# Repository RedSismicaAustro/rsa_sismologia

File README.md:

# RSA Sismología (`rsa_sismologia`)

Sistema de análisis sismológico, procesamiento de señales sísmicas (MiniSEED/EVT), marcado de fases y generación de boletines oficiales de la Red Sísmica del Austro (RSA).

---

## 📚 Documentación y Manuales del Sistema

- **Manual y Reglas del Agente**: [`AGENTS.md`](file:///c:/proyectos/rsa_sismologia/AGENTS.md)
- **Contexto Técnico Maestro**: [`docs/contexto_maestro_agente.md`](file:///c:/proyectos/rsa_sismologia/docs/contexto_maestro_agente.md)
- **Estructura de Datos `DIA`**: [`docs/contexto_estructura_datos_dia.md`](file:///c:/proyectos/rsa_sismologia/docs/contexto_estructura_datos_dia.md)
- **Archivos de Configuración**: [`docs/contexto_archivos_configuracion_datos.md`](file:///c:/proyectos/rsa_sismologia/docs/contexto_archivos_configuracion_datos.md)

---

## 🔄 Protocolo de Sesión con Agentes IA

### 🟢 Inicio de Sesión (Scope Lock):
```text
Considera las reglas y skills definidos en .agents/rules y .agents/skills.
Para esta sesión, nuestro directorio de trabajo exclusivo será [DIRECTORIO]. No modifiques ni busques archivos fuera de esta ruta a menos que te lo pida. 
Revisa los archivos del directorio [DIRECTORIO] para que entiendas el contexto actual del proyecto. Todavia no modifiques ni crees ningun archivo.
```

### 🔴 Cierre de Sesión:
1. `Genera o actualiza el contexto tecnico de los archivos que fueron modificados durante la sesión, según la skill generar_contexto.md.`
2. `Extrae o actualiza el ADR de las decisiones tomadas durante la sesión, según la skill extraer_adr.md.`
3. `Genera la transición técnica de esta sesión según la skill crear_transicion_tecnica.md.`
4. `Genera un resumen detallado de todos los cambios y archivos modificados durante esta sesión.`

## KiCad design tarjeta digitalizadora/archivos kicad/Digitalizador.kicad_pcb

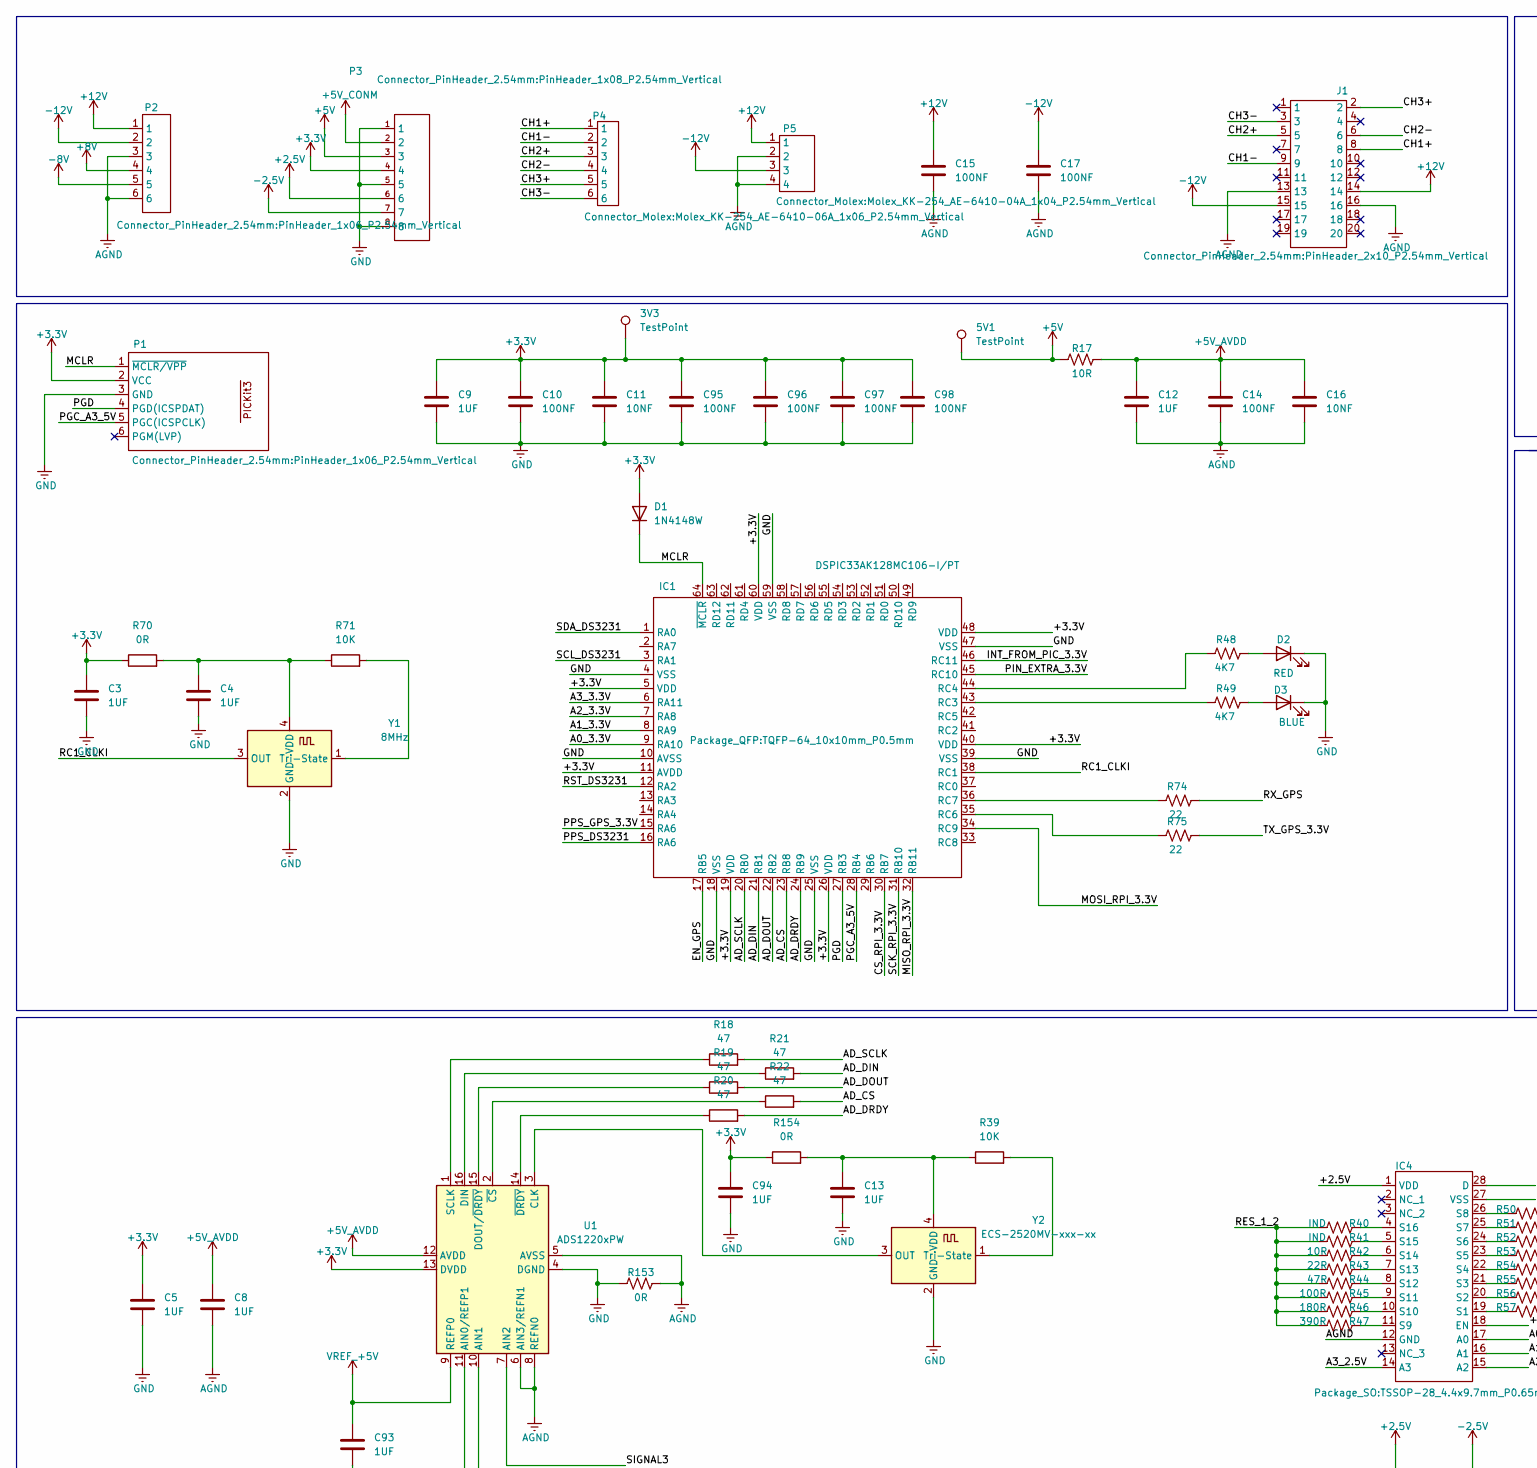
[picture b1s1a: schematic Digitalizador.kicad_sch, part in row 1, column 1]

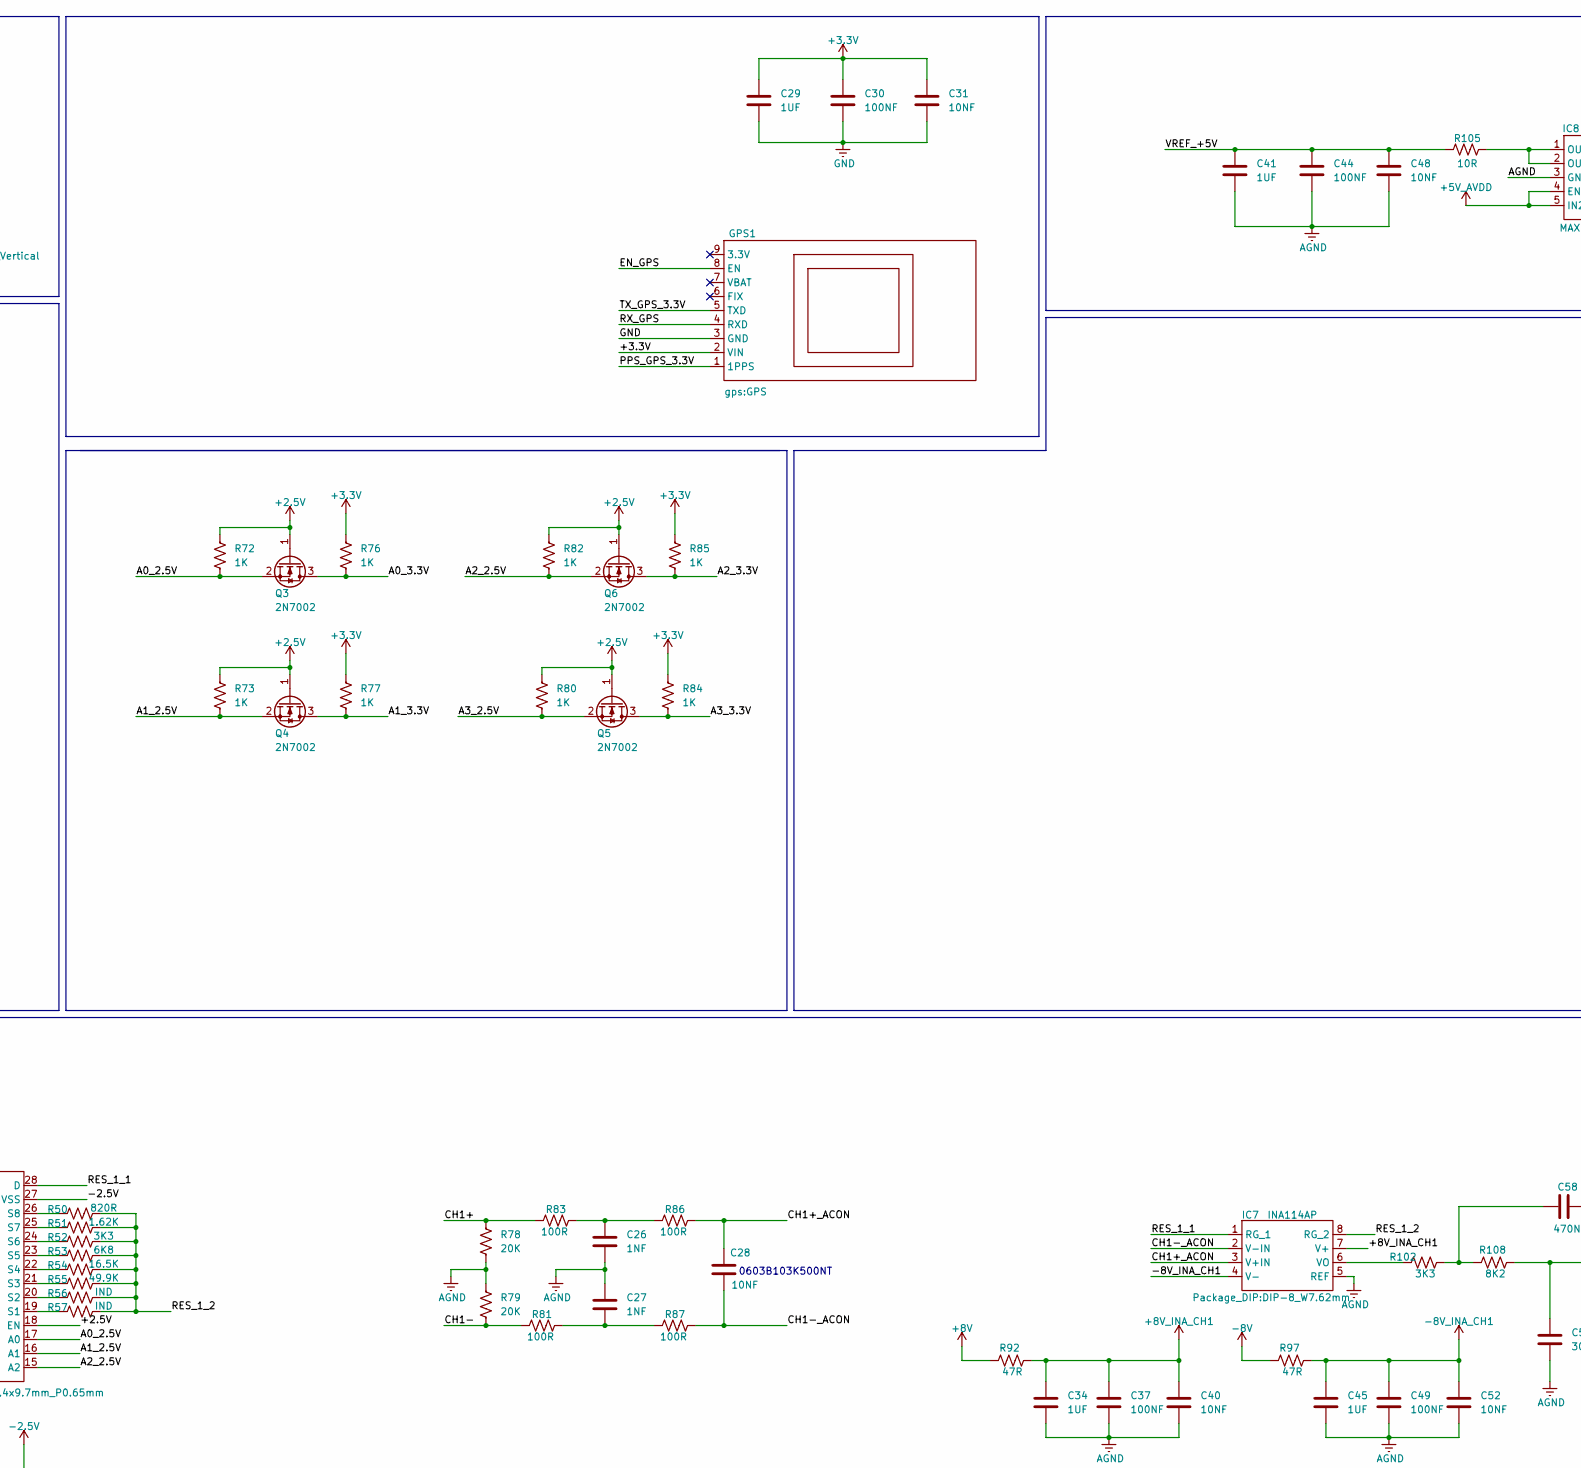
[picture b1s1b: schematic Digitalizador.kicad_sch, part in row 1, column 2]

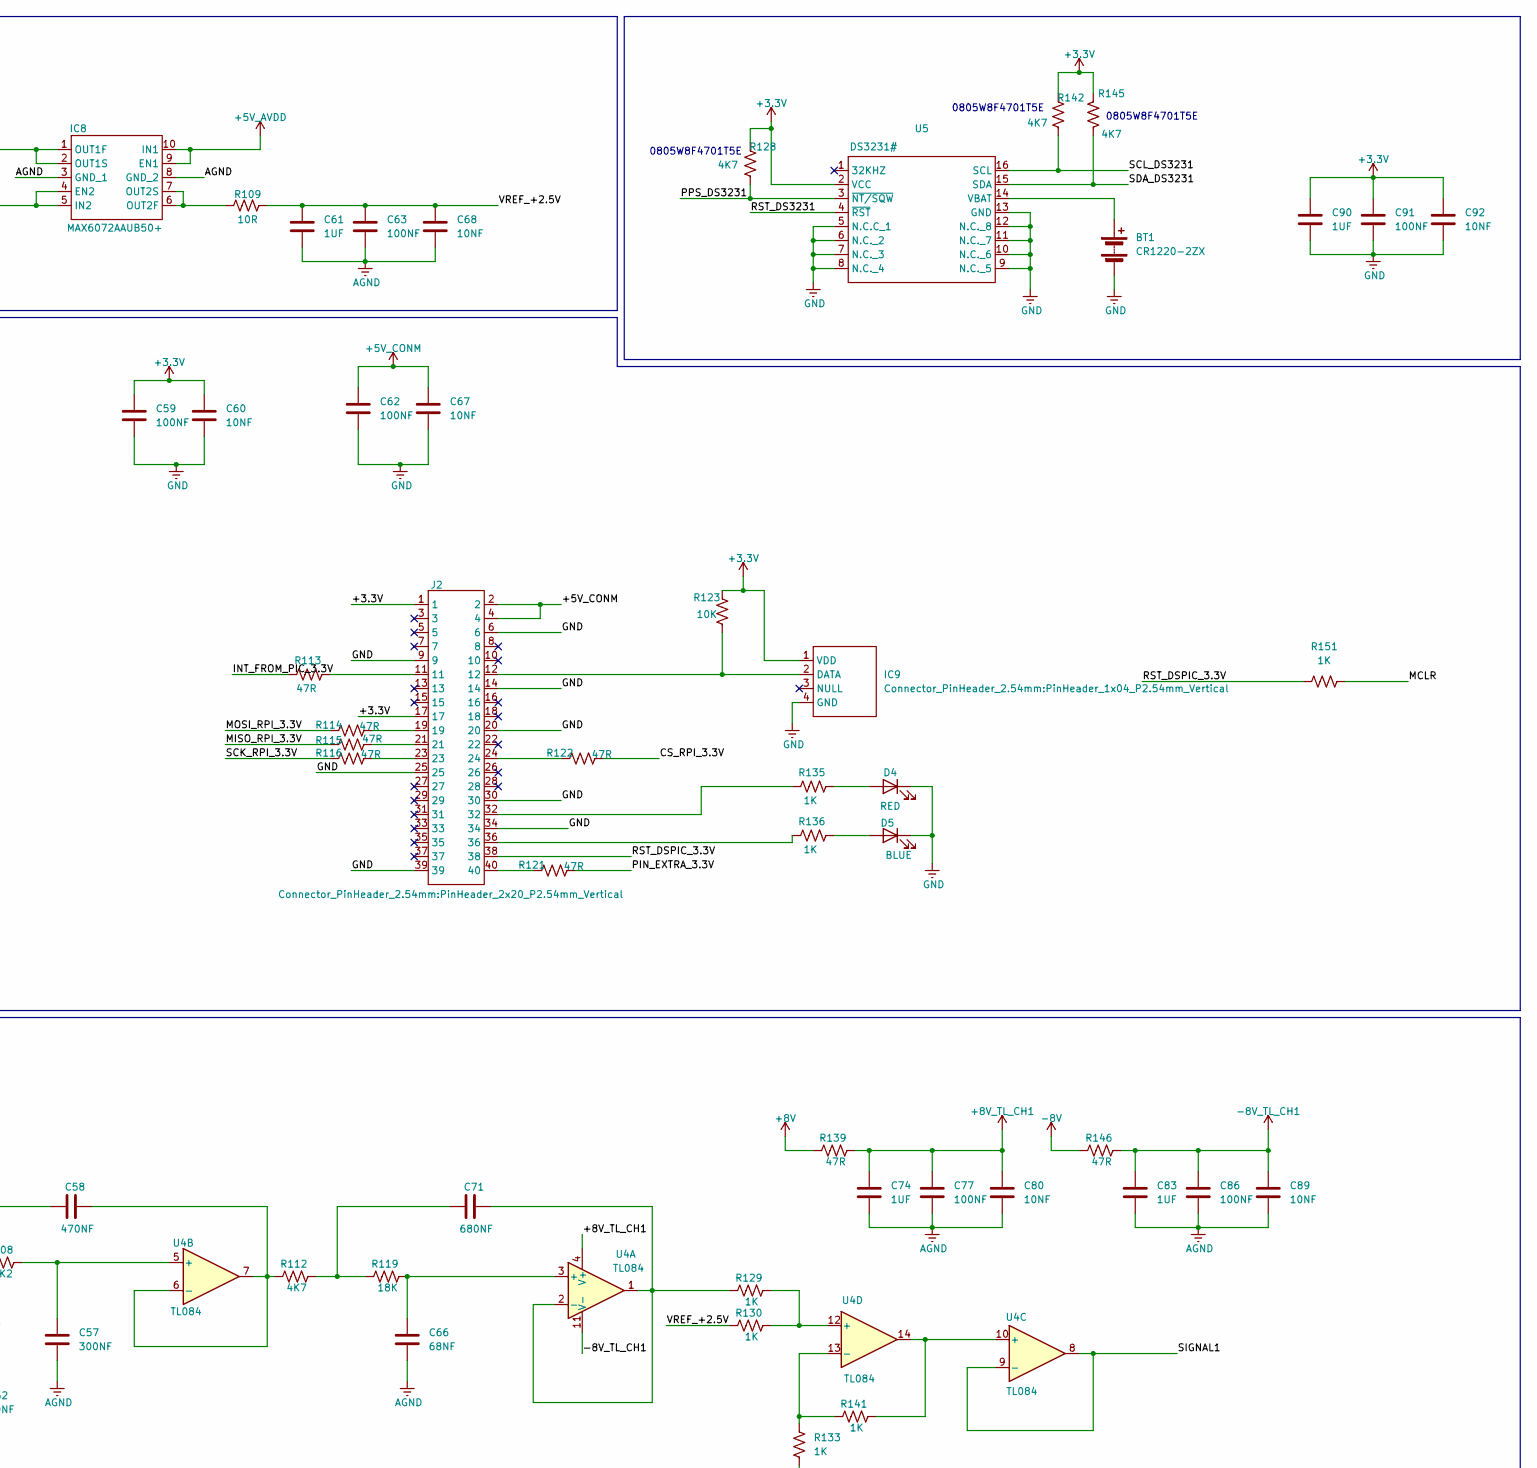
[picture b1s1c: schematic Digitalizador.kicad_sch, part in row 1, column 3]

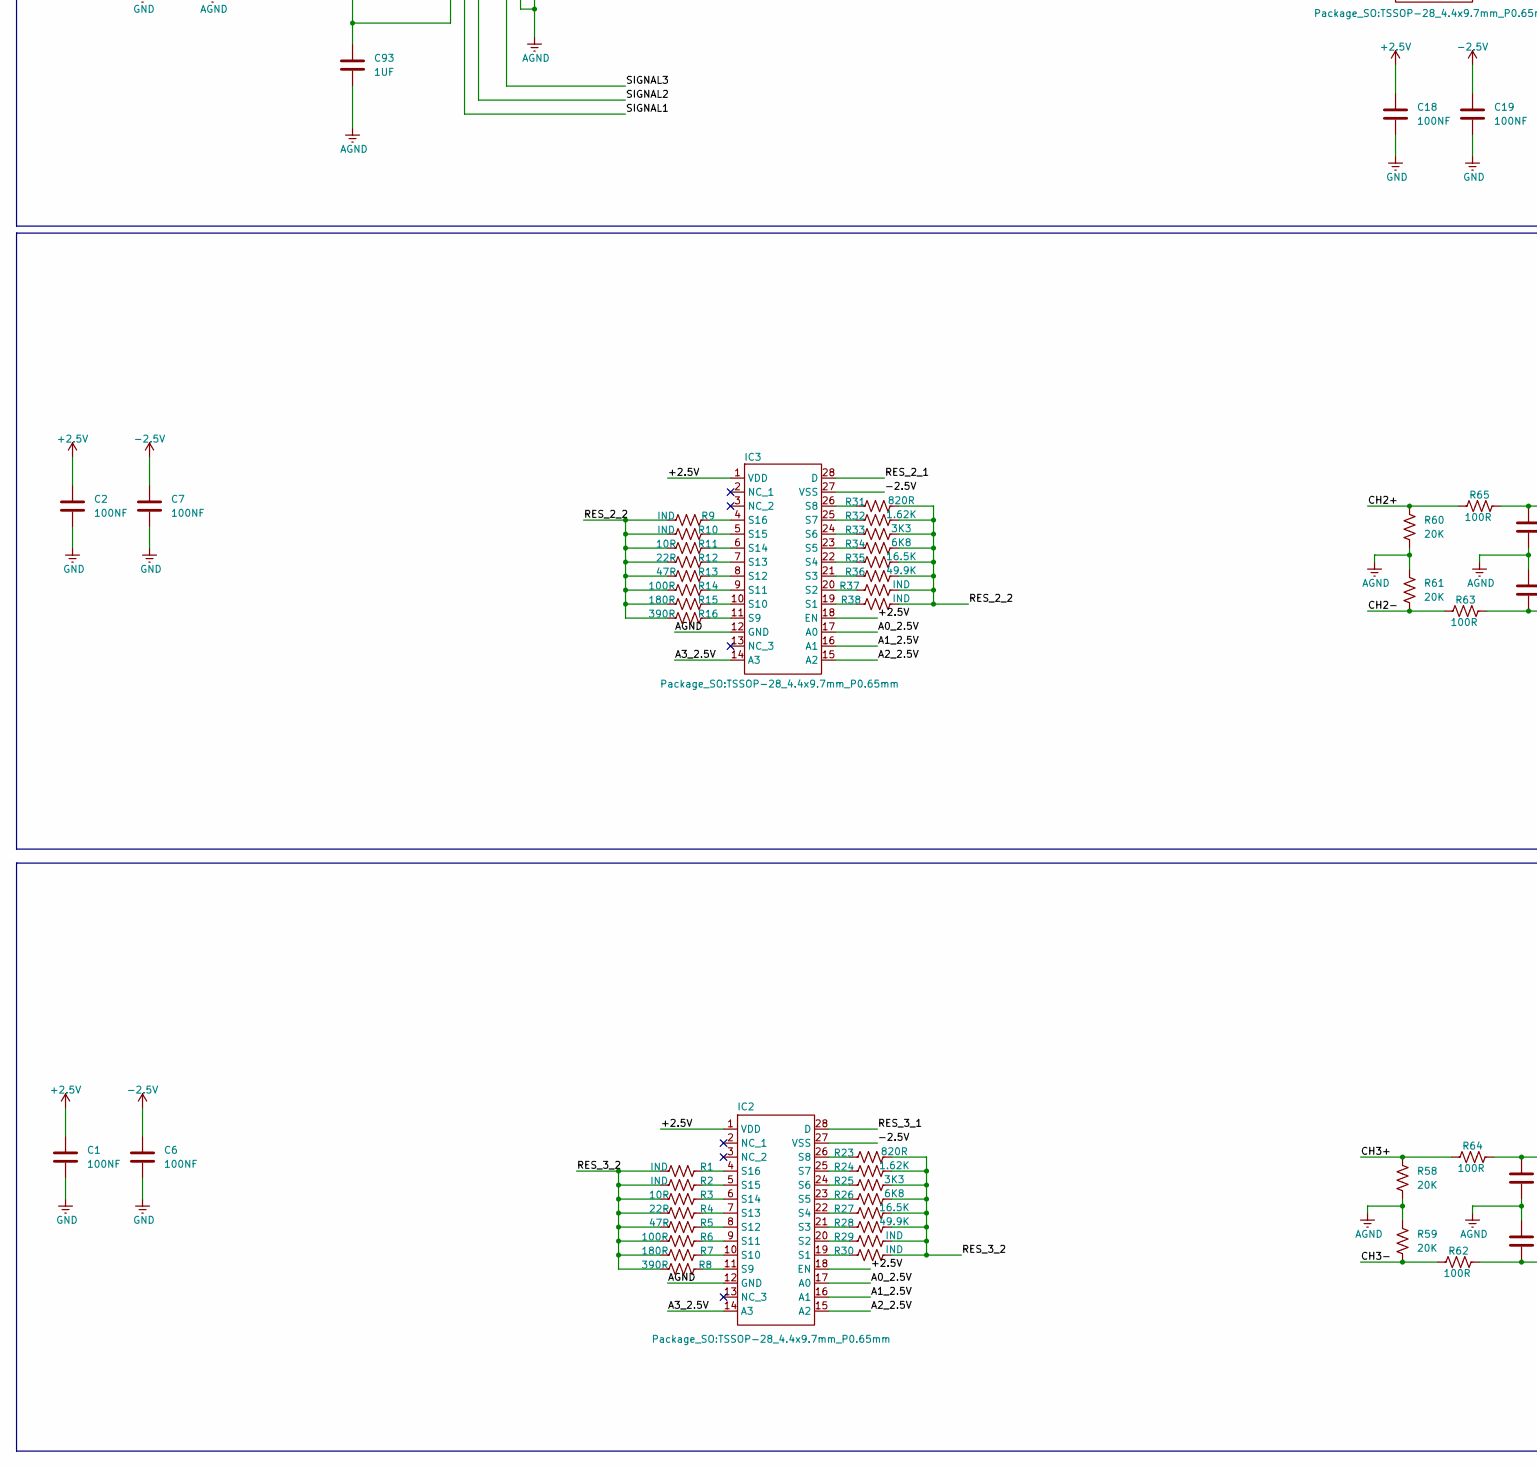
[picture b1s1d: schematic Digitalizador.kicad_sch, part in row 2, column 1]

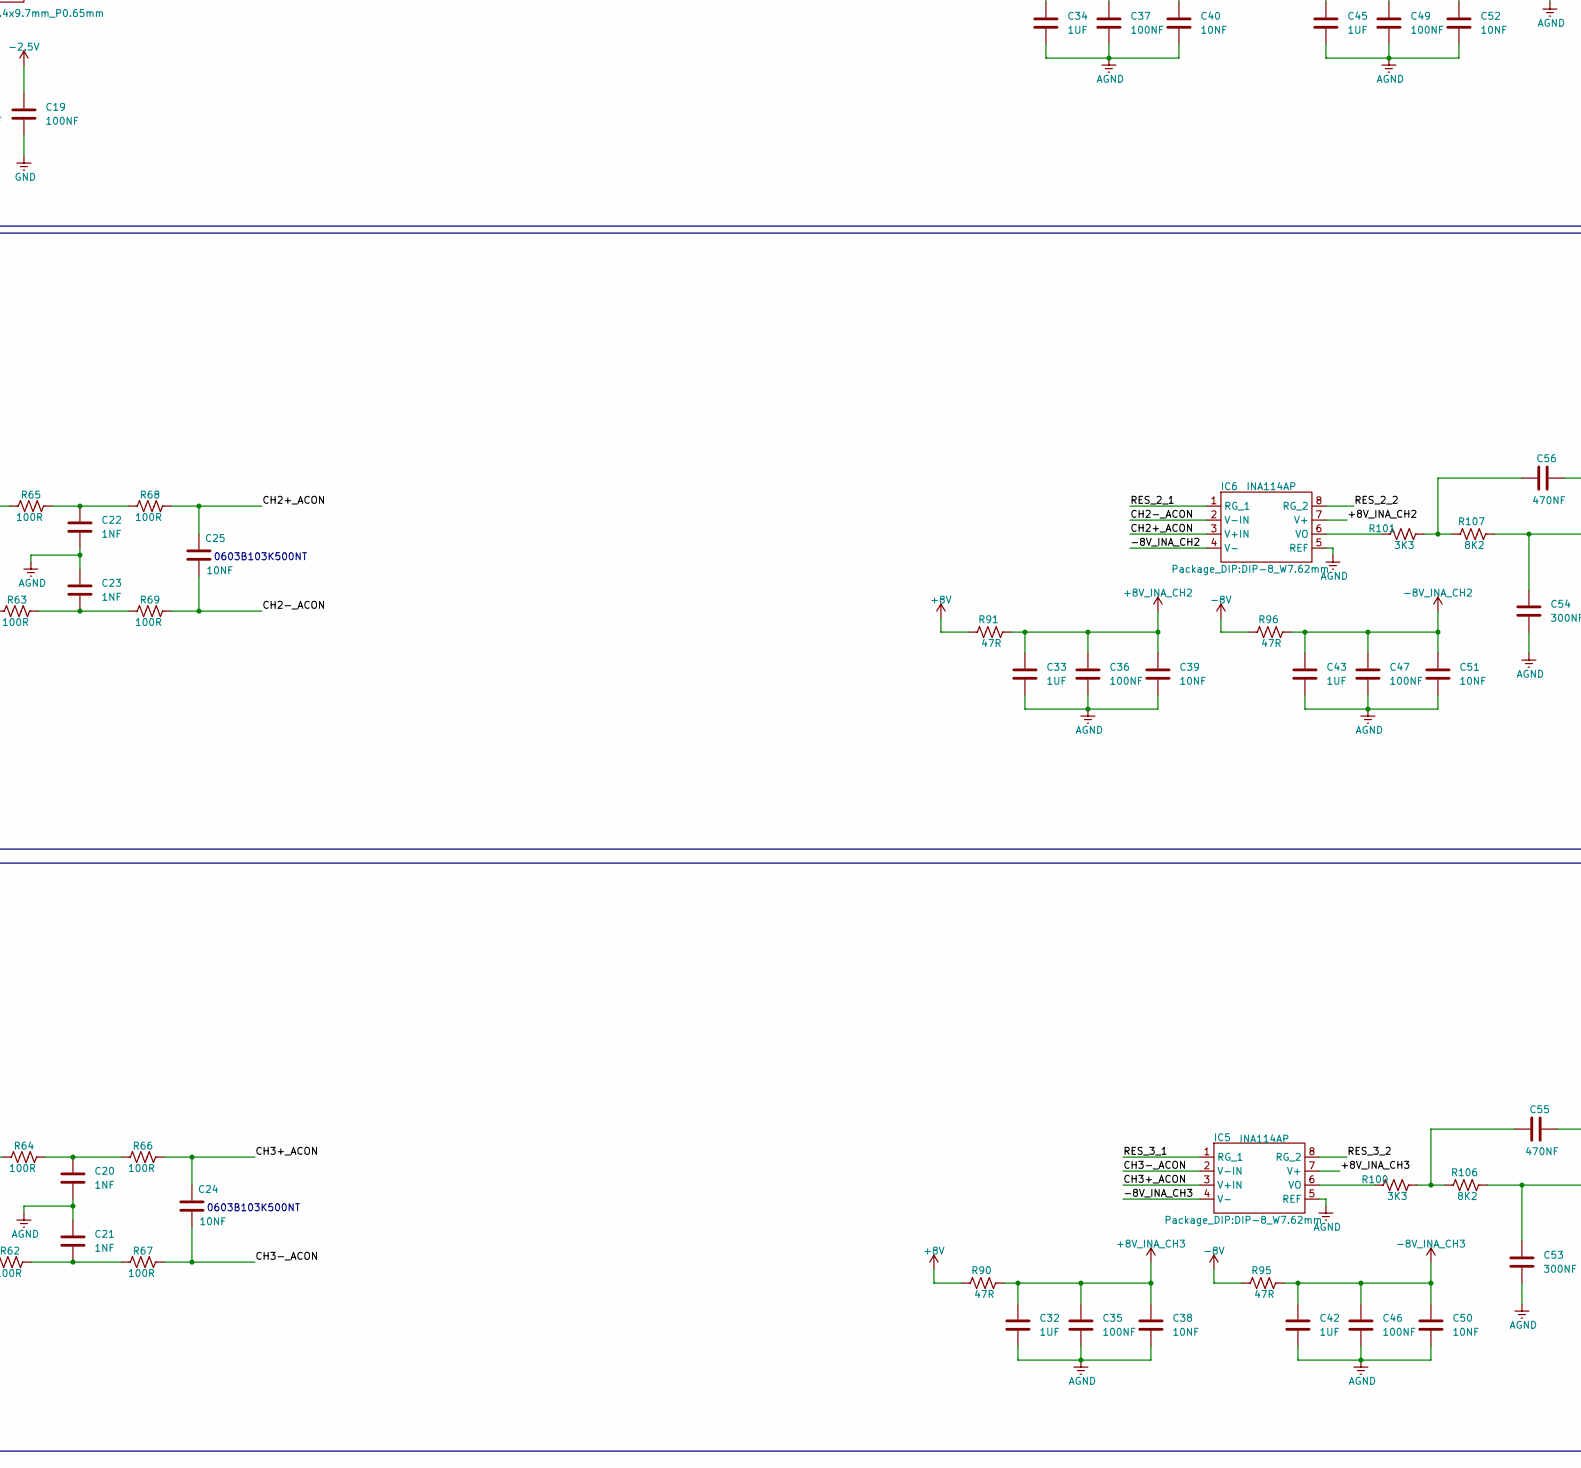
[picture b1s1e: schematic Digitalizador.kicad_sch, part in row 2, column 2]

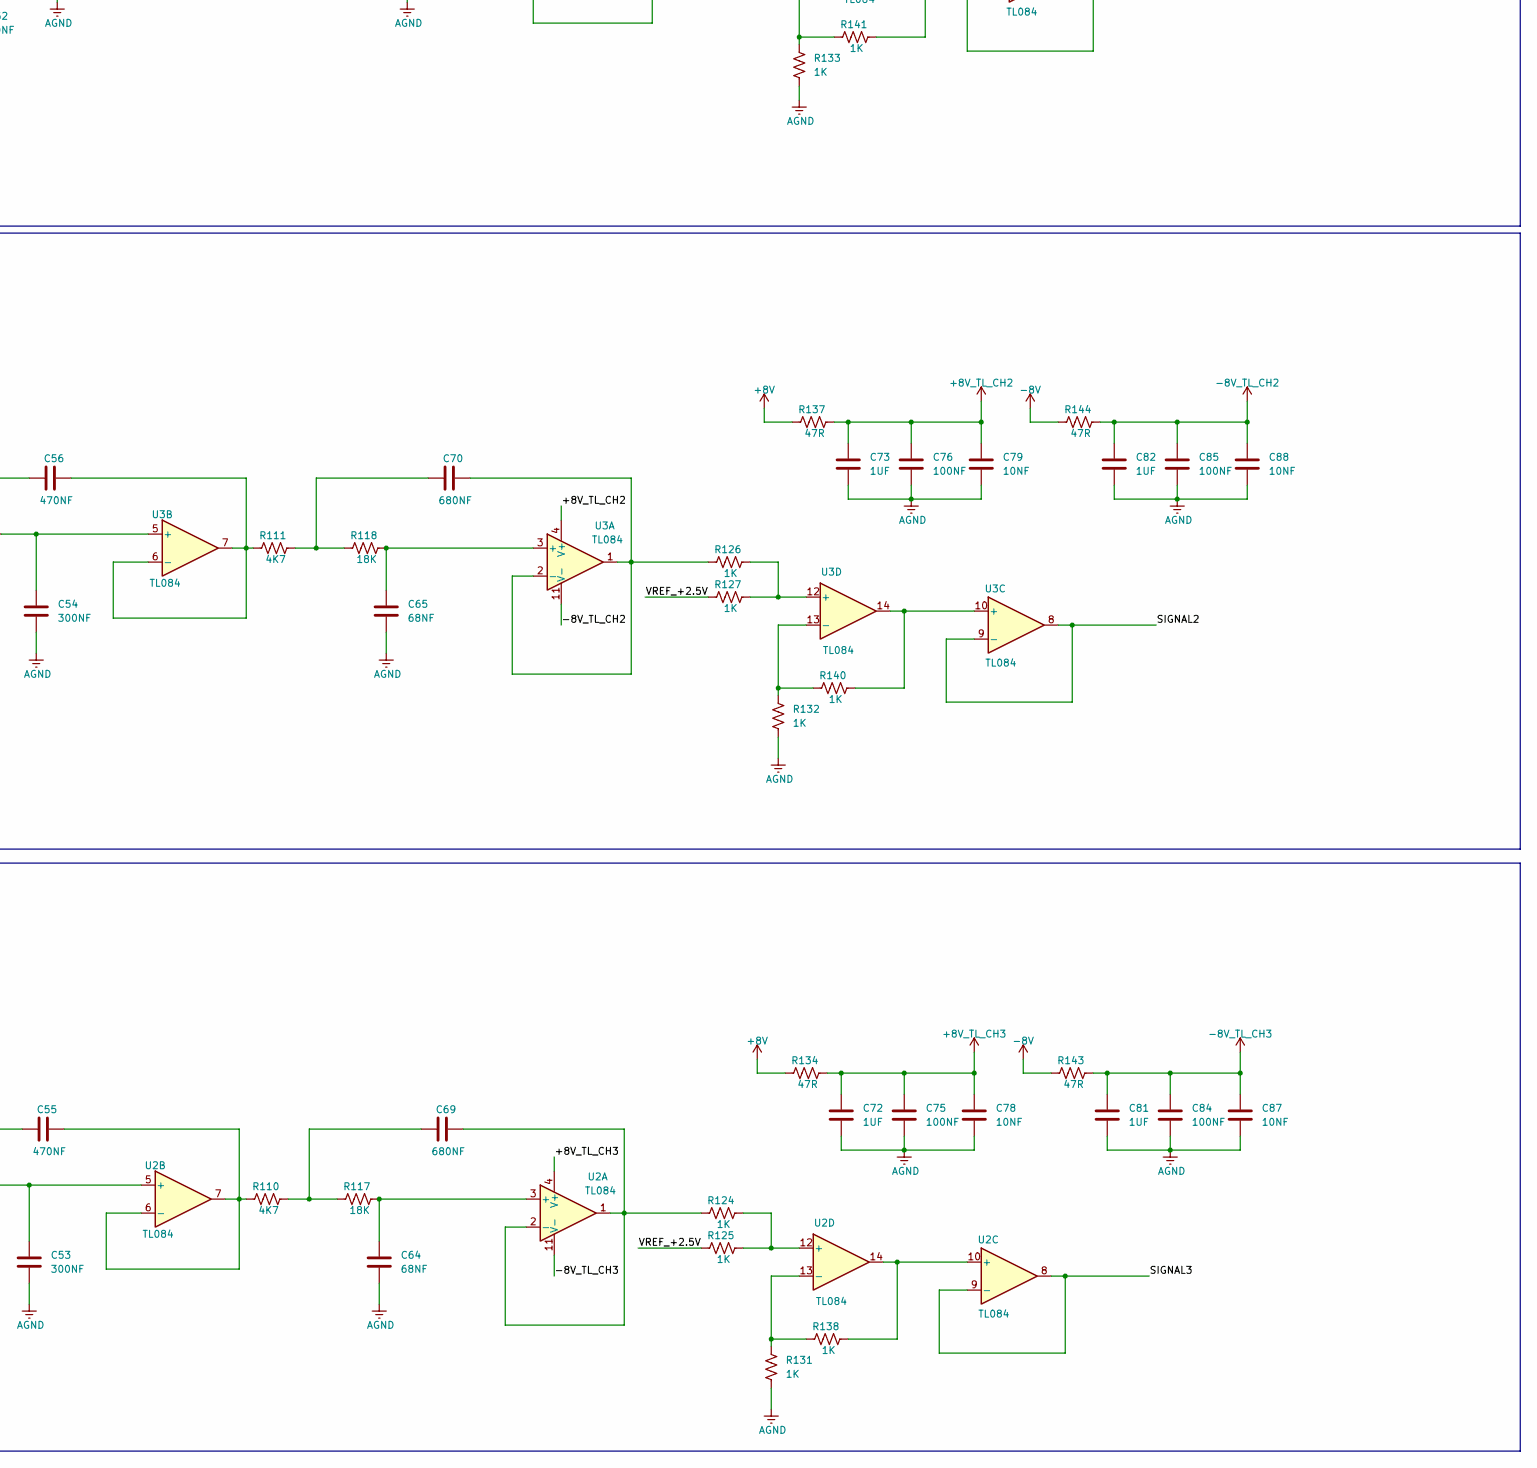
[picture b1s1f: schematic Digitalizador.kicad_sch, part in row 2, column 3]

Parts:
3V3, 5V1: TestPoint; Pin_D1.0mm_L10.0mm
BT1: CR1220-2ZX; CR12202
C1, C2, C6, C7, C10, C14, C15, C17, C18, C19, C30, C35, C36, C37, C44, C46, C47, C49, C59, C62, C63, C75, C76, C77, C84, C85, C86, C91, C95, C96, C97, C98: 100NF; C_0603_1608Metric
C3, C4, C5, C8, C9, C12, C13, C29, C32, C33, C34, C41, C42, C43, C45, C61, C72, C73, C74, C81, C82, C83, C90, C93, C94: 1UF; C_0603_1608Metric
C11, C16, C24, C25, C28, C31, C38, C39, C40, C48, C50, C51, C52, C60, C67, C68, C78, C79, C80, C87, C88, C89, C92: 10NF; C_0603_1608Metric
C20, C21, C22, C23, C26, C27: 1NF; C_0603_1608Metric
C53, C54, C57: 300NF; C_0603_1608Metric
C55, C56, C58: 470NF; C_0603_1608Metric
C64, C65, C66: 68NF; C_0603_1608Metric
C69, C70, C71: 680NF; C_0603_1608Metric
D1: 1N4148W; D_SOD-123
D2, D4: RED; LED_0603_1608Metric
D3, D5: BLUE; LED_0603_1608Metric
GPS1: GPS
IC1: DSPIC33AK128MC106-I/PT; TQFP-64_10x10mm_P0.5mm
IC2, IC3, IC4: TSSOP-28_4.4x9.7mm_P0.65mm
IC5, IC6, IC7: INA114AP; DIP-8_W7.62mm
IC8: MAX6072AAUB50+
IC9: PinHeader_1x04_P2.54mm_Vertical
J1: PinHeader_2x10_P2.54mm_Vertical
J2: PinHeader_2x20_P2.54mm_Vertical
P1, P2: PinHeader_1x06_P2.54mm_Vertical
P3: PinHeader_1x08_P2.54mm_Vertical
P4: Molex_KK-254_AE-6410-06A_1x06_P2.54mm_Vertical
P5: Molex_KK-254_AE-6410-04A_1x04_P2.54mm_Vertical
Q3, Q4, Q5, Q6: 2N7002; SOT-23
R1, R2, R9, R10, R29, R30, R37, R38, R40, R41, R56, R57: IND; R_0603_1608Metric
R3, R11, R17, R42, R105, R109: 10R; R_0603_1608Metric
R4, R12, R43: 22R; R_0603_1608Metric
R5, R13, R44, R90, R91, R92, R95, R96, R97, R113, R114, R115, R116, R121, R122, R134, R137, R139, R143, R144, R146: 47R; R_0603_1608Metric
R6, R14, R45, R62, R63, R64, R65, R66, R67, R68, R69, R81, R83, R86, R87: 100R; R_0603_1608Metric
R7, R15, R46: 180R; R_0603_1608Metric
R8, R16, R47: 390R; R_0603_1608Metric
R18, R19, R20, R21, R22: 47; R_0603_1608Metric
R23, R31, R50: 820R; R_0603_1608Metric
R24, R32, R51: 1.62K; R_0603_1608Metric
R25, R33, R52, R100, R101, R102: 3K3; R_0603_1608Metric
R26, R34, R53: 6K8; R_0603_1608Metric
R27, R35, R54: 16.5K; R_0603_1608Metric
R28, R36, R55: 49.9K; R_0603_1608Metric
R39, R71, R123: 10K; R_0603_1608Metric
R48, R49, R110, R111, R112, R128, R142, R145: 4K7; R_0603_1608Metric
R58, R59, R60, R61, R78, R79: 20K; R_0603_1608Metric
R70, R153, R154: 0R; R_0603_1608Metric
R72, R73, R76, R77, R80, R82, R84, R85, R124, R125, R126, R127, R129, R130, R131, R132, R133, R135, R136, R138, R140, R141, R151: 1K; R_0603_1608Metric
R74, R75: 22; R_0603_1608Metric
R106, R107, R108: 8K2; R_0603_1608Metric
R117, R118, R119: 18K; R_0603_1608Metric
U1: ADS1220xPW; TSSOP-16_4.4x5mm_P0.65mm
U2, U3, U4: TL084; SOIC-14_3.9x8.7mm_P1.27mm
U5: DS3231#; SOIC-16W_7.5x10.3mm_P1.27mm
Y1: 8MHz; Oscillator_SMD_ECS_2520MV-xxx-xx-4Pin_2.5x2.0mm
Y2: ECS-2520MV-xxx-xx; Oscillator_SMD_ECS_2520MV-xxx-xx-4Pin_2.5x2.0mm

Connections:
+2.5V: C1.1, C2.1, C18.1, IC2.1 (VDD), IC2.18 (EN), IC3.1 (VDD), IC3.18 (EN), IC4.1 (VDD), IC4.18 (EN), P3.6, Q3.1 (G), Q4.1 (G), Q5.1 (G), Q6.1 (G), R72.1, R73.1, R80.1, R82.1
+3.3V: 3V3.1, C3.1, C5.1, C9.1, C10.1, C11.1, C29.1, C30.1, C31.1, C59.1, C60.1, C90.1, C91.1, C92.1, C94.1, C95.1, C96.1, C97.1, C98.1, D1.2 (A), GPS1.2 (VIN), IC1.5 (VDD), IC1.11 (AVDD), IC1.19 (VDD), IC1.26 (VDD), IC1.40 (VDD), IC1.48 (VDD), IC1.60 (VDD), IC9.1 (VDD), J2.1, J2.17, P1.2 (VCC), P3.4, R70.1, R76.1, R77.1, R84.1, R85.1, R123.1, R128.1, R142.1, R145.1, R154.1, U1.13 (DVDD), U5.2 (VCC)
+5V: 5V1.1, P3.3, R17.1
+5V_AVDD: C8.1, C12.1, C14.1, C16.1, IC8.4 (EN2), IC8.5 (IN2), IC8.9 (EN1), IC8.10 (IN1), R17.2, U1.12 (AVDD)
+5V_CONM: C62.1, C67.1, J2.2, J2.4, P3.2
+8V: P2.4, R90.1, R91.1, R92.1, R134.1, R137.1, R139.1
+8V_INA_CH1: C34.1, C37.1, C40.1, IC7.7 (V+), R92.2
+8V_INA_CH2: C33.1, C36.1, C39.1, IC6.7 (V+), R91.2
+8V_INA_CH3: C32.1, C35.1, C38.1, IC5.7 (V+), R90.2
+8V_TL_CH1: C74.1, C77.1, C80.1, R139.2, U4.4 (V+)
+8V_TL_CH2: C73.1, C76.1, C79.1, R137.2, U3.4 (V+)
+8V_TL_CH3: C72.1, C75.1, C78.1, R134.2, U2.4 (V+)
+12V: C15.1, J1.14, P2.1, P5.1
-2.5V: C6.1, C7.1, C19.1, IC2.27 (VSS), IC3.27 (VSS), IC4.27 (VSS), P3.7
-8V: P2.5, R95.1, R96.1, R97.1, R143.1, R144.1, R146.1
-8V_INA_CH1: C45.1, C49.1, C52.1, IC7.4 (V-), R97.2
-8V_INA_CH2: C43.1, C47.1, C51.1, IC6.4 (V-), R96.2
-8V_INA_CH3: C42.1, C46.1, C50.1, IC5.4 (V-), R95.2
-8V_TL_CH1: C83.1, C86.1, C89.1, R146.2, U4.11 (V-)
-8V_TL_CH2: C82.1, C85.1, C88.1, R144.2, U3.11 (V-)
-8V_TL_CH3: C81.1, C84.1, C87.1, R143.2, U2.11 (V-)
-12V: C17.1, J1.15, P2.2, P5.3
/A0_2.5V: IC2.17 (A0), IC3.17 (A0), IC4.17 (A0), Q3.2 (S), R72.2
/A0_3.3V: IC1.9 (RA10), Q3.3 (D), R76.2
/A1_2.5V: IC2.16 (A1), IC3.16 (A1), IC4.16 (A1), Q4.2 (S), R73.2
/A1_3.3V: IC1.8 (RA9), Q4.3 (D), R77.2
/A2_2.5V: IC2.15 (A2), IC3.15 (A2), IC4.15 (A2), Q6.2 (S), R82.2
/A2_3.3V: IC1.7 (RA8), Q6.3 (D), R85.2
/A3_2.5V: IC2.14 (A3), IC3.14 (A3), IC4.14 (A3), Q5.2 (S), R80.2
/A3_3.3V: IC1.6 (RA11), Q5.3 (D), R84.2
/AD_CS: IC1.23 (RB8), R22.2
/AD_DIN: IC1.21 (RB1), R21.2
/AD_DOUT: IC1.22 (RB2), R19.2
/AD_DRDY: IC1.24 (RB9), R20.2
/AD_SCLK: IC1.20 (RB0), R18.2
/CH1+: J1.8, P4.1, R78.1, R83.1
/CH1+_ACON: C28.1, IC7.3 (V+IN), R86.2
/CH1-: J1.9, P4.2, R79.2, R81.1
/CH1-_ACON: C28.2, IC7.2 (V-IN), R87.2
/CH2+: J1.5, P4.3, R60.1, R65.1
/CH2+_ACON: C25.1, IC6.3 (V+IN), R68.2
/CH2-: J1.6, P4.4, R61.2, R63.1
/CH2-_ACON: C25.2, IC6.2 (V-IN), R69.2
/CH3+: J1.2, P4.5, R58.1, R64.1
/CH3+_ACON: C24.1, IC5.3 (V+IN), R66.2
/CH3-: J1.3, P4.6, R59.2, R62.1
/CH3-_ACON: C24.2, IC5.2 (V-IN), R67.2
/CS_RPI_3.3V: IC1.30 (RB7), R122.2
/EN_GPS: GPS1.8 (EN), IC1.17 (RB5)
/INT_FROM_PIC_3.3V: IC1.46 (RC11), R113.1
/MCLR: D1.1 (K), IC1.64 (~MCLR), P1.1 (~MCLR/VPP), R151.2
/MISO_RPI_3.3V: IC1.32 (RB11), R115.1
/MOSI_RPI_3.3V: IC1.34 (RC9), R114.1
/PGC_A3_5V: IC1.28 (RB4), P1.5 (PGC(ICSPCLK))
/PGD: IC1.27 (RB3), P1.4 (PGD(ICSPDAT))
/PIN_EXTRA_3.3V: IC1.45 (RC10), R121.2
/PPS_DS3231: IC1.16 (RA6), R128.2, U5.3 (~NT/SQW)
/PPS_GPS_3.3V: GPS1.1 (1PPS), IC1.15 (RA6)
/RC1_CLKI: IC1.38 (RC1), Y1.3 (OUT)
/RES_1_1: IC4.28 (D), IC7.1 (RG_1)
/RES_1_2: IC7.8 (RG_2), R40.1, R41.1, R42.1, R43.1, R44.1, R45.1, R46.1, R47.1, R50.2, R51.2, R52.2, R53.2, R54.2, R55.2, R56.2, R57.2
/RES_2_1: IC3.28 (D), IC6.1 (RG_1)
/RES_2_2: IC6.8 (RG_2), R9.1, R10.1, R11.1, R12.1, R13.1, R14.1, R15.1, R16.1, R31.2, R32.2, R33.2, R34.2, R35.2, R36.2, R37.2, R38.2
/RES_3_1: IC2.28 (D), IC5.1 (RG_1)
/RES_3_2: IC5.8 (RG_2), R1.1, R2.1, R3.1, R4.1, R5.1, R6.1, R7.1, R8.1, R23.2, R24.2, R25.2, R26.2, R27.2, R28.2, R29.2, R30.2
/RST_DS3231: IC1.12 (RA2), U5.4 (~RST)
/RST_DSPIC_3.3V: J2.38, R151.1
/RX_GPS: GPS1.4 (RXD), R74.2
/SCK_RPI_3.3V: IC1.31 (RB10), R116.1
/SCL_DS3231: IC1.3 (RA1), R142.2, U5.16 (SCL)
/SDA_DS3231: IC1.1 (RA0), R145.2, U5.15 (SDA)
/SIGNAL1: U1.11 (AIN0/REFP1), U4.8, U4.9 (-)
/SIGNAL2: U1.10 (AIN1), U3.8, U3.9 (-)
/SIGNAL3: U1.7 (AIN2), U2.8, U2.9 (-)
/TX_GPS_3.3V: GPS1.5 (TXD), R75.2
/VREF_+2.5V: C61.1, C63.1, C68.1, R109.2, R125.1, R127.1, R130.1
AGND: C8.2, C12.2, C14.2, C15.2, C16.2, C17.2, C20.2, C21.1, C22.2, C23.1, C26.2, C27.1, C32.2, C33.2, C34.2, C35.2, C36.2, C37.2, C38.2, C39.2, C40.2, C41.2, C42.2, C43.2, C44.2, C45.2, C46.2, C47.2, C48.2, C49.2, C50.2, C51.2, C52.2, C53.2, C54.2, C57.2, C61.2, C63.2, C64.2, C65.2, C66.2, C68.2, C72.2, C73.2, C74.2, C75.2, C76.2, C77.2, C78.2, C79.2, C80.2, C81.2, C82.2, C83.2, C84.2, C85.2, C86.2, C87.2, C88.2, C89.2, C93.2, IC2.12 (GND), IC3.12 (GND), IC4.12 (GND), IC5.5 (REF), IC6.5 (REF), IC7.5 (REF), IC8.3 (GND_1), IC8.8 (GND_2), J1.13, J1.16, P2.3, P2.6, P5.2, P5.4, R58.2, R59.1, R60.2, R61.1, R78.2, R79.1, R131.2, R132.2, R133.2, R153.2, U1.5 (AVSS), U1.6 (AIN3/REFN1), U1.8 (REFN0)
GND: BT1.2 (-), C1.2, C2.2, C3.2, C4.2, C5.2, C6.2, C7.2, C9.2, C10.2, C11.2, C13.2, C18.2, C19.2, C29.2, C30.2, C31.2, C59.2, C60.2, C62.2, C67.2, C90.2, C91.2, C92.2, C94.2, C95.2, C96.2, C97.2, C98.2, D2.1 (K), D3.1 (K), D4.1 (K), D5.1 (K), GPS1.3 (GND), IC1.4 (VSS), IC1.10 (AVSS), IC1.18 (VSS), IC1.25 (VSS), IC1.39 (VSS), IC1.47 (VSS), IC1.59 (VSS), IC9.4 (GND), J2.6, J2.9, J2.14, J2.20, J2.25, J2.30, J2.34, J2.39, P1.3 (GND), P3.1, P3.5, P3.8, R153.1, U1.4 (DGND), U5.5 (N.C.C_1), U5.6 (N.C._2), U5.7 (N.C._3), U5.8 (N.C._4), U5.9 (N.C._5), U5.10 (N.C._6), U5.11 (N.C._7), U5.12 (N.C._8), U5.13 (GND), Y1.2 (GND), Y2.2 (GND)
unnamed: BT1.1 (+), U5.14 (VBAT)
unnamed: C20.1, R64.2, R66.1
unnamed: C21.2, R62.2, R67.1
unnamed: C22.1, R65.2, R68.1
unnamed: C23.2, R63.2, R69.1
unnamed: C26.1, R83.2, R86.1
unnamed: C27.2, R81.2, R87.1
unnamed: C55.2, R100.2, R106.1
unnamed: C56.2, R101.2, R107.1
unnamed: C58.2, R102.2, R108.1
unnamed: C69.2, R110.2, R117.1
unnamed: C70.2, R111.2, R118.1
unnamed: C71.2, R112.2, R119.1
unnamed: D2.2 (A), R48.2
unnamed: D3.2 (A), R49.2
unnamed: D4.2 (A), R135.2
unnamed: D5.2 (A), R136.2
unnamed: IC1.43 (RC3), R49.1
unnamed: IC1.44 (RC4), R48.1
unnamed: IC1.35 (RC6), R75.1
unnamed: IC1.36 (RC7), R74.1
unnamed: IC2.19 (S1), R30.1
unnamed: IC2.20 (S2), R29.1
unnamed: IC2.21 (S3), R28.1
unnamed: IC2.22 (S4), R27.1
unnamed: IC2.23 (S5), R26.1
unnamed: IC2.24 (S6), R25.1
unnamed: IC2.25 (S7), R24.1
unnamed: IC2.26 (S8), R23.1
unnamed: IC2.11 (S9), R8.2
unnamed: IC2.10 (S10), R7.2
unnamed: IC2.9 (S11), R6.2
unnamed: IC2.8 (S12), R5.2
unnamed: IC2.7 (S13), R4.2
unnamed: IC2.6 (S14), R3.2
unnamed: IC2.5 (S15), R2.2
unnamed: IC2.4 (S16), R1.2
unnamed: IC3.19 (S1), R38.1
unnamed: IC3.20 (S2), R37.1
unnamed: IC3.21 (S3), R36.1
unnamed: IC3.22 (S4), R35.1
unnamed: IC3.23 (S5), R34.1
unnamed: IC3.24 (S6), R33.1
unnamed: IC3.25 (S7), R32.1
unnamed: IC3.26 (S8), R31.1
unnamed: IC3.11 (S9), R16.2
unnamed: IC3.10 (S10), R15.2
unnamed: IC3.9 (S11), R14.2
unnamed: IC3.8 (S12), R13.2
unnamed: IC3.7 (S13), R12.2
unnamed: IC3.6 (S14), R11.2
unnamed: IC3.5 (S15), R10.2
unnamed: IC3.4 (S16), R9.2
unnamed: IC4.19 (S1), R57.1
unnamed: IC4.20 (S2), R56.1
unnamed: IC4.21 (S3), R55.1
unnamed: IC4.22 (S4), R54.1
unnamed: IC4.23 (S5), R53.1
unnamed: IC4.24 (S6), R52.1
unnamed: IC4.25 (S7), R51.1
unnamed: IC4.26 (S8), R50.1
unnamed: IC4.11 (S9), R47.2
unnamed: IC4.10 (S10), R46.2
unnamed: IC4.9 (S11), R45.2
unnamed: IC4.8 (S12), R44.2
unnamed: IC4.7 (S13), R43.2
unnamed: IC4.6 (S14), R42.2
unnamed: IC4.5 (S15), R41.2
unnamed: IC4.4 (S16), R40.2
unnamed: IC5.6 (VO), R100.1
unnamed: IC6.6 (VO), R101.1
unnamed: IC7.6 (VO), R102.1
unnamed: IC8.1 (OUT1F), IC8.2 (OUT1S), R105.2
unnamed: IC8.6 (OUT2F), IC8.7 (OUT2S), R109.1
unnamed: IC9.2 (DATA), J2.12, R123.2
unnamed: J2.11, R113.2
unnamed: J2.19, R114.2
unnamed: J2.21, R115.2
unnamed: J2.23, R116.2
unnamed: J2.24, R122.1
unnamed: J2.32, R135.1
unnamed: J2.36, R136.1
unnamed: J2.40, R121.1
unnamed: U1.3 (CLK), Y2.3 (OUT)
unnamed: R21.1, U1.16 (DIN)
unnamed: R19.1, U1.15 (DOUT/~DRDY)
unnamed: R18.1, U1.1 (SCLK)
unnamed: R22.1, U1.2 (~CS)
unnamed: R20.1, U1.14 (~DRDY)
unnamed: C64.1, R117.2, U2.3 (+)
unnamed: C69.1, R124.1, U2.1, U2.2 (-)
unnamed: C53.1, R106.2, U2.5 (+)
unnamed: C55.1, R110.1, U2.6 (-), U2.7
unnamed: R138.2, U2.10 (+), U2.14
unnamed: R124.2, R125.2, U2.12 (+)
unnamed: R131.1, R138.1, U2.13 (-)
unnamed: C65.1, R118.2, U3.3 (+)
unnamed: C70.1, R126.1, U3.1, U3.2 (-)
unnamed: C54.1, R107.2, U3.5 (+)
unnamed: C56.1, R111.1, U3.6 (-), U3.7
unnamed: R140.2, U3.10 (+), U3.14
unnamed: R126.2, R127.2, U3.12 (+)
unnamed: R132.1, R140.1, U3.13 (-)
unnamed: C66.1, R119.2, U4.3 (+)
unnamed: C71.1, R129.1, U4.1, U4.2 (-)
unnamed: C57.1, R108.2, U4.5 (+)
unnamed: C58.1, R112.1, U4.6 (-), U4.7
unnamed: R141.2, U4.10 (+), U4.14
unnamed: R129.2, R130.2, U4.12 (+)
unnamed: R133.1, R141.1, U4.13 (-)
unnamed: R71.2, Y1.1 (Tri-State)
unnamed: C4.1, R70.2, R71.1, Y1.4 (VDD)
unnamed: R39.2, Y2.1 (Tri-State)
unnamed: C13.1, R39.1, R154.2, Y2.4 (VDD)
VREF_+5V: C41.1, C44.1, C48.1, C93.1, R105.1, U1.9 (REFP0)

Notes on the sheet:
0805W8F4701T5E
0603B103K500NT
